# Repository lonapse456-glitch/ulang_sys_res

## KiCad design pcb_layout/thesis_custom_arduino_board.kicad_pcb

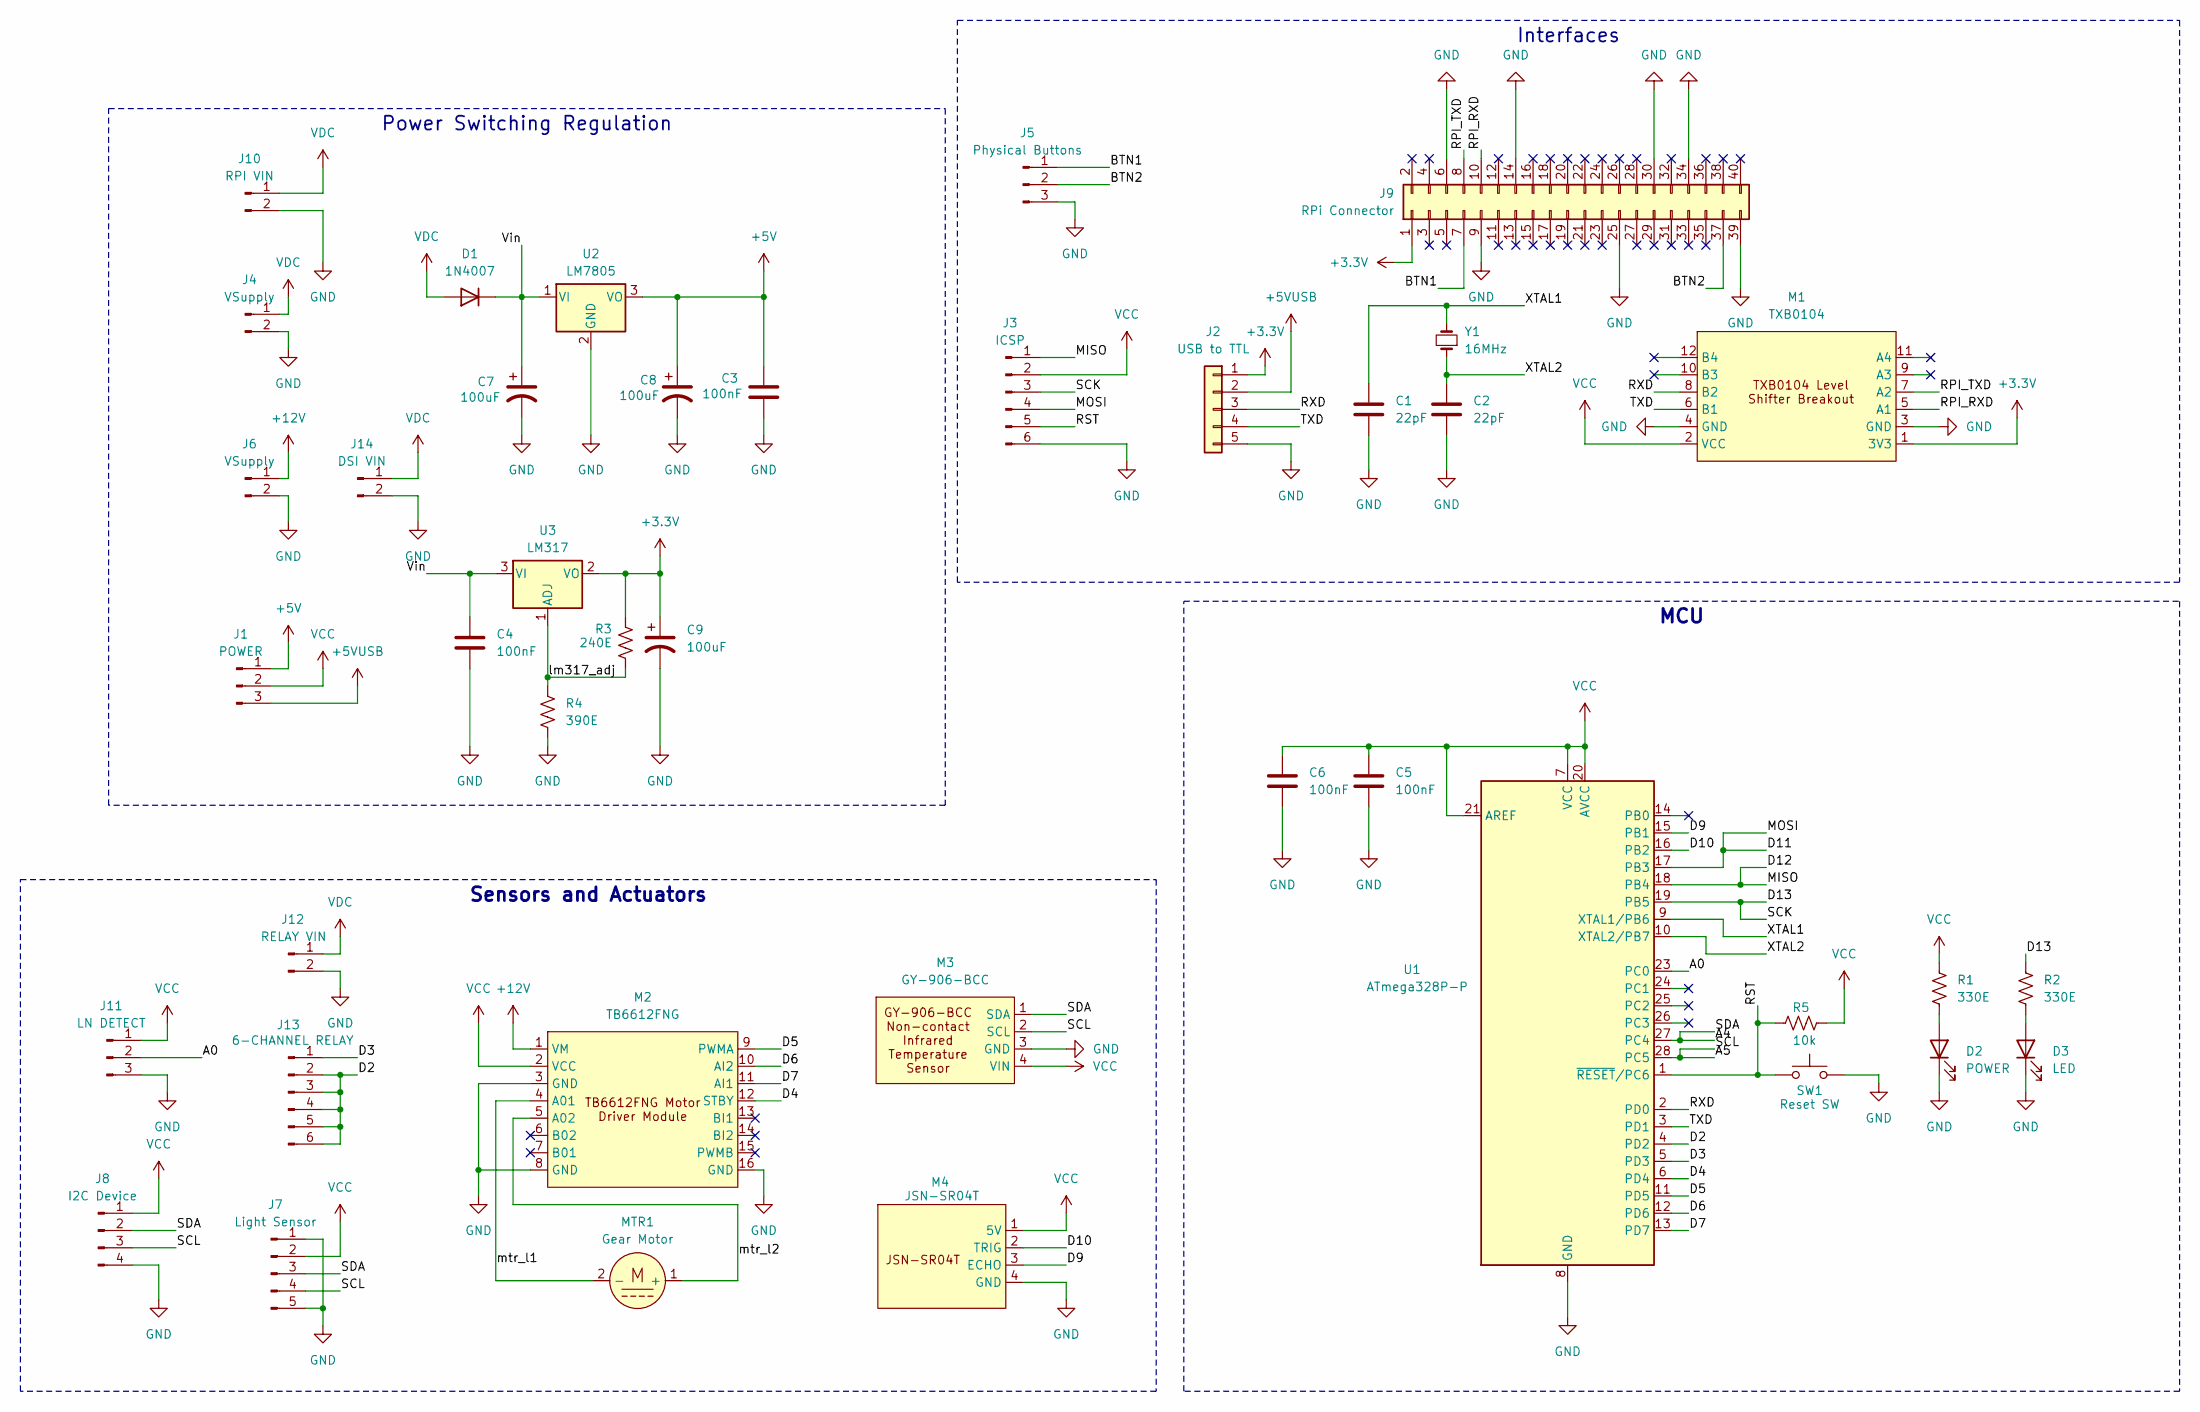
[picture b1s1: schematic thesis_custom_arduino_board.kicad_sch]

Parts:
C1, C2: 22pF; C_Disc_D5.0mm_W2.5mm_P5.00mm
C3, C4, C5, C6: 100nF; C_Disc_D5.0mm_W2.5mm_P5.00mm
C7, C8, C9: 100uF; CP_Radial_D5.0mm_P2.00mm
D1: 1N4007; D_DO-41_SOD81_P10.16mm_Horizontal
D2: POWER; LED_D5.0mm
D3: LED; LED_D5.0mm
J1: POWER; PinHeader_1x03_P2.54mm_Vertical
J2: USB to TTL; JST_XH_B5B-XH-A_1x05_P2.50mm_Vertical
J3: ICSP; JST_XH_B6B-XH-A_1x06_P2.50mm_Vertical
J4: VSupply; JST_VH_B2P-VH-B_1x02_P3.96mm_Vertical
J5: Physical Buttons; JST_XH_B3B-XH-A_1x03_P2.50mm_Vertical
J6: VSupply; JST_XH_B2B-XH-A_1x02_P2.50mm_Vertical
J7: Light Sensor; JST_XH_B5B-XH-A_1x05_P2.50mm_Vertical
J8: I2C Device; JST_XH_B4B-XH-A_1x04_P2.50mm_Vertical
J9: RPi Connector; 2x20_Shrouded
J10: RPI VIN; JST_VH_B2P-VH-B_1x02_P3.96mm_Vertical
J11: LN DETECT; JST_XH_B3B-XH-A_1x03_P2.50mm_Vertical
J12: RELAY VIN; JST_XH_B2B-XH-A_1x02_P2.50mm_Vertical
J13: 6-CHANNEL RELAY; JST_XH_B6B-XH-A_1x06_P2.50mm_Vertical
J14: DSI VIN; JST_XH_B2B-XH-A_1x02_P2.50mm_Vertical
M1: TXB0104; TXB0104 Module
M2: TB6612FNG; TB6612FNG Module
M3: GY-906-BCC; JST_XH_B4B-XH-A_1x04_P2.50mm_Vertical
M4: JSN-SR04T; JST_XH_B4B-XH-A_1x04_P2.50mm_Vertical
MTR1: Gear Motor; JST_XH_B2B-XH-A_1x02_P2.50mm_Vertical
R1, R2: 330E; R_Axial_DIN0207_L6.3mm_D2.5mm_P7.62mm_Horizontal
R3: 240E; R_Axial_DIN0207_L6.3mm_D2.5mm_P7.62mm_Horizontal
R4: 390E; R_Axial_DIN0207_L6.3mm_D2.5mm_P7.62mm_Horizontal
R5: 10k; R_Axial_DIN0207_L6.3mm_D2.5mm_P7.62mm_Horizontal
SW1: Reset SW; SW_PUSH_6mm_H5mm
U1: ATmega328P-P; DIP-28_W7.62mm_Socket
U2: LM7805; TO-220-3_Vertical
U3: LM317; TO-220-3_Vertical
Y1: 16MHz; Crystal_HC49-4H_Vertical

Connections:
+3.3V: C9.1, J2.1, J9.1 (2Pin_a1), M1.1 (3V3), R3.1, U3.2 (VO)
+5V: C3.1, C8.1, J1.1, U2.3 (VO)
+5VUSB: J1.3, J2.2
+12V: J6.1, M2.1 (VM)
/A0: J11.2, U1.23 (PC0)
/A4: J7.3, J8.2, M3.1 (SDA), U1.27 (PC4)
/A5: J7.4, J8.3, M3.2 (SCL), U1.28 (PC5)
/BTN1: J5.1, J9.7 (Pin_a4)
/BTN2: J5.2, J9.37 (Pin_a19)
/D2: J13.2, J13.3, J13.4, J13.5, J13.6, U1.4 (PD2)
/D3: J13.1, U1.5 (PD3)
/D4: M2.12 (STBY), U1.6 (PD4)
/D5: M2.9 (PWMA), U1.11 (PD5)
/D6: M2.10 (AI2), U1.12 (PD6)
/D7: M2.11 (AI1), U1.13 (PD7)
/D9: M4.3 (ECHO), U1.15 (PB1)
/D10: M4.2 (TRIG), U1.16 (PB2)
/D11: J3.4, U1.17 (PB3)
/D12: J3.1, U1.18 (PB4)
/D13: J3.3, R2.1, U1.19 (PB5)
/RPI_RXD: J9.10 (Pin_b5), M1.5 (A1)
/RPI_TXD: J9.8 (Pin_b4), M1.7 (A2)
/RST: J3.5, R5.2, SW1.1, U1.1 (~RESET/PC6)
/RXD: J2.3, M1.8 (B2), U1.2 (PD0)
/TXD: J2.4, M1.6 (B1), U1.3 (PD1)
/Vin: C4.1, C7.1, D1.1 (K), U2.1 (VI), U3.3 (VI)
/XTAL1: C1.1, U1.9 (XTAL1/PB6), Y1.2
/XTAL2: C2.1, U1.10 (XTAL2/PB7), Y1.1
/lm317_adj: R3.2, R4.1, U3.1 (ADJ)
/mtr_l1: M2.4 (A01), MTR1.2 (-)
/mtr_l2: M2.5 (A02), MTR1.1 (+)
GND: C1.2, C2.2, C3.2, C4.2, C5.2, C6.2, C7.2, C8.2, C9.2, D2.1 (K), D3.1 (K), J2.5, J3.6, J4.2, J5.3, J6.2, J7.1, J7.5, J8.4, J9.6 (Pin_b3), J9.9 (Pin_a5), J9.14 (Pin_b7), J9.25 (Pin_a13), J9.30 (Pin_b15), J9.34 (Pin_b17), J9.39 (Pin_a20), J10.2, J11.3, J12.2, J14.2, M1.3 (GND), M1.4 (GND), M2.3 (GND), M2.8 (GND), M2.16 (GND), M3.3 (GND), M4.4 (GND), R4.2, SW1.2, U1.8 (GND), U1.22 (GND), U2.2 (GND)
unnamed: D2.2 (A), R1.2
unnamed: D3.2 (A), R2.2
VCC: C5.1, C6.1, J1.2, J3.2, J7.2, J8.1, J11.1, M1.2 (VCC), M2.2 (VCC), M3.4 (VIN), M4.1 (5V), R1.1, R5.1, U1.7 (VCC), U1.20 (AVCC), U1.21 (AREF)
VDC: D1.2 (A), J4.1, J10.1, J12.1, J14.1

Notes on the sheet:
MCU
Interfaces
Sensors and Actuators
Power Switching Regulation

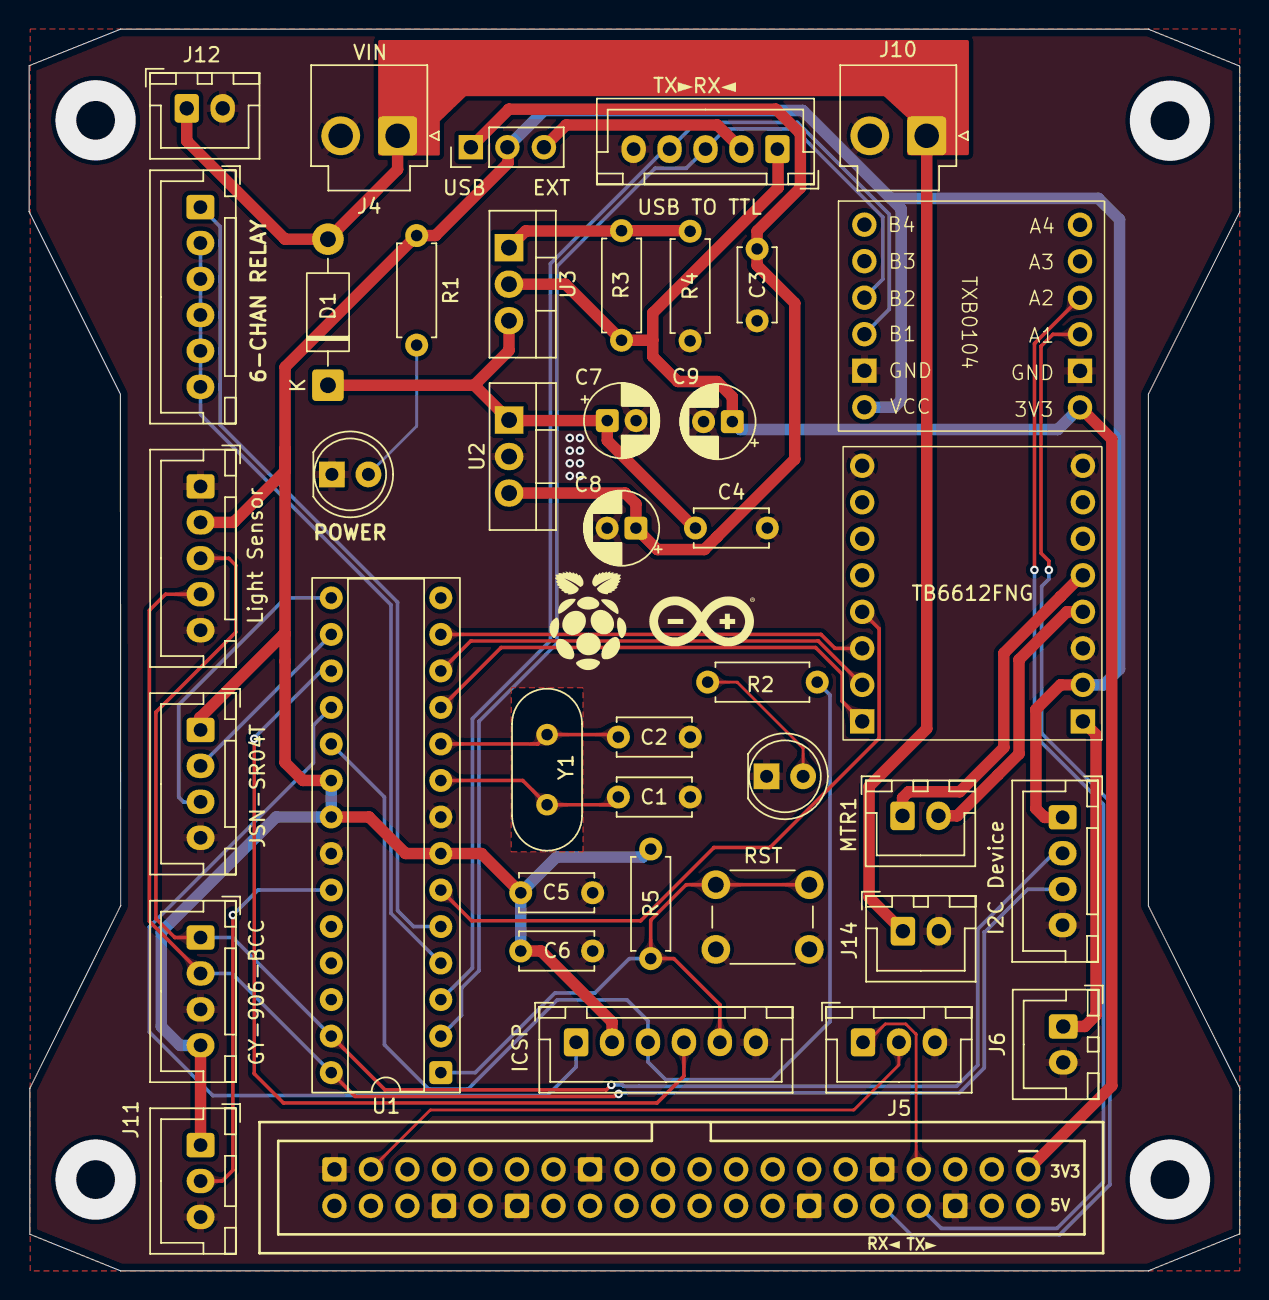
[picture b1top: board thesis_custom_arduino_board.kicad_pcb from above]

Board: 2 copper layers, 84.2 x 86.4 mm, 41 parts (0 on the bottom side), 36 nets.

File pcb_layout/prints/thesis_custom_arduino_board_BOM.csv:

"Id";"Designator";"Footprint";"Quantity";"Designation";"Supplier and ref";
1;"J9";"2x20_Shrouded";1;"RPi Connector";;;
2;"J8";"JST_XH_B4B-XH-A_1x04_P2.50mm_Vertical";1;"I2C Device";;;
3;"J7";"JST_XH_B5B-XH-A_1x05_P2.50mm_Vertical";1;"Light Sensor";;;
4;"12V,J4";"JST_XH_B2B-XH-A_1x02_P2.50mm_Vertical";2;"VSupply";;;
5;"R4";"R_Axial_DIN0207_L6.3mm_D2.5mm_P7.62mm_Horizontal";1;"390E";;;
6;"M2";"TB6612FNG Module";1;"TB6612FNG";;;
7;"Y1";"Crystal_HC49-4H_Vertical";1;"16MHz";;;
8;"C8,C9,C7";"CP_Radial_D5.0mm_P2.00mm";3;"100uF";;;
9;"J3";"JST_XH_B6B-XH-A_1x06_P2.50mm_Vertical";1;"ICSP";;;
10;"D2";"LED_D5.0mm";1;"POWER";;;
11;"M3";"JST_XH_B4B-XH-A_1x04_P2.50mm_Vertical";1;"GY-906-BCC";;;
12;"J5";"JST_XH_B8B-XH-A_1x08_P2.50mm_Vertical";1;"6-channel Relay";;;
13;"C3,C4,C5,C6";"C_Disc_D5.0mm_W2.5mm_P5.00mm";4;"100nF";;;
14;"U1";"DIP-28_W7.62mm_Socket";1;"ATmega328P-P";;;
15;"R1,R2";"R_Axial_DIN0207_L6.3mm_D2.5mm_P7.62mm_Horizontal";2;"330E";;;
16;"D3";"LED_D5.0mm";1;"LED";;;
17;"C1,C2";"C_Disc_D5.0mm_W2.5mm_P5.00mm";2;"22pF";;;
18;"R3";"R_Axial_DIN0207_L6.3mm_D2.5mm_P7.62mm_Horizontal";1;"240E";;;
19;"U3";"TO-220-3_Vertical";1;"LM317";;;
20;"M4";"JST_XH_B4B-XH-A_1x04_P2.50mm_Vertical";1;"JSN-SR04T";;;
21;"J1";"PinHeader_1x03_P2.54mm_Vertical";1;"POWER";;;
22;"J2";"JST_XH_B5B-XH-A_1x05_P2.50mm_Vertical";1;"USB to TTL";;;
23;"MTR";"JST_XH_B2B-XH-A_1x02_P2.50mm_Vertical";1;"Gear Motor";;;
24;"U2";"TO-220-3_Vertical";1;"LM7805";;;
25;"R5";"R_Axial_DIN0207_L6.3mm_D2.5mm_P7.62mm_Horizontal";1;"10k";;;
26;"D1";"D_DO-41_SOD81_P10.16mm_Horizontal";1;"1N4007";;;
27;"SW1";"SW_PUSH_6mm_H5mm";1;"Reset SW";;;
28;"M1";"TXB0104 Module";1;"TXB0104";;;
